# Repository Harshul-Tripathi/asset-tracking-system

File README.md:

# Anti-Theft Tracking

An industrial project developed in collaboration with **STMicroelectronics** to design and implement a highly accurate, multi-anchor asset tracking and anti-theft system utilizing Ultra-Wideband (UWB) technology that offers centimeter-level precision. 

This repository contains the complete firmware, hardware PCB designs, and comprehensive documentation for the entire project lifecycle.

---
## 👥 Contributors

*   Krishang Singh - Hardware selection, Schematic and Layout design, Low-power optimization
*   Krishna Kumar Mahto - Firmware, Qorvo SDK, Breadboard testing (one way ranging)
*   Harshul Tripathi - MCU Pinout Architecture (CubeMX), AirTag Analysis, System Power Profiling

## 🏗️ System Architecture

The tracking ecosystem relies on a 4-subsystem architecture designed for precise trilateration and efficient power management. The system consists of three stationary anchors and one mobile tag:

### 1. STM32 Anchor (Hub)
*   **Hardware:** NUCLEO-U575ZI-Q + BU03 (UWB Module) + ST67W611M (Wi-Fi Module)
*   **Role:** Acts as the central hub of the tracking system. It interfaces with the tag and the secondary ESP32 anchors to compute the final location of the asset and manage the network. It publishes this data to a dashboard through the ST67W611M Wi-Fi module.
*   **Location:** `firmware/stm32-anchor-hub/nucleo-u575zi-q_bu03/`

### 2. ESP32 Anchors (x2)
*   **Hardware:** ESP32 + UWB Modules
*   **Role:** Two secondary stationary anchors strategically placed to provide the additional reference points required for accurate 2D/3D trilateration. 
*   **Location:** `firmware/esp32-anchors/`

### 3. STM32 Tag
*   **Hardware:** NUCLEO-WBA55CG + BU03 (UWB Module) / Custom Compact PCB
*   **Role:** The mobile asset being tracked. Designed for a compact footprint, it broadcasts its signals to the anchor network.
*   **Location:** `firmware/stm32-tag/Nucleo-WBA55CG_BU03/`

---

## 📂 Repository Structure

The repository is modularized to separate different microcontrollers, hardware designs, and documentation, preventing workspace conflicts.

*   **`/docs`**: Contains all reference materials, component datasheets, project presentations, and research (including AirTag teardowns).
*   **`/firmware`**: Separated source code for the ESP-IDF and STM32CubeIDE workspaces. Each subsystem contains its own build instructions and configurations.
*   **`/hardware`**: Contains the custom compact tag PCB designs (KiCad/Altium). Includes standard EDA source files alongside a `/production` folder for manufacturing Gerbers and BOMs.
  ---

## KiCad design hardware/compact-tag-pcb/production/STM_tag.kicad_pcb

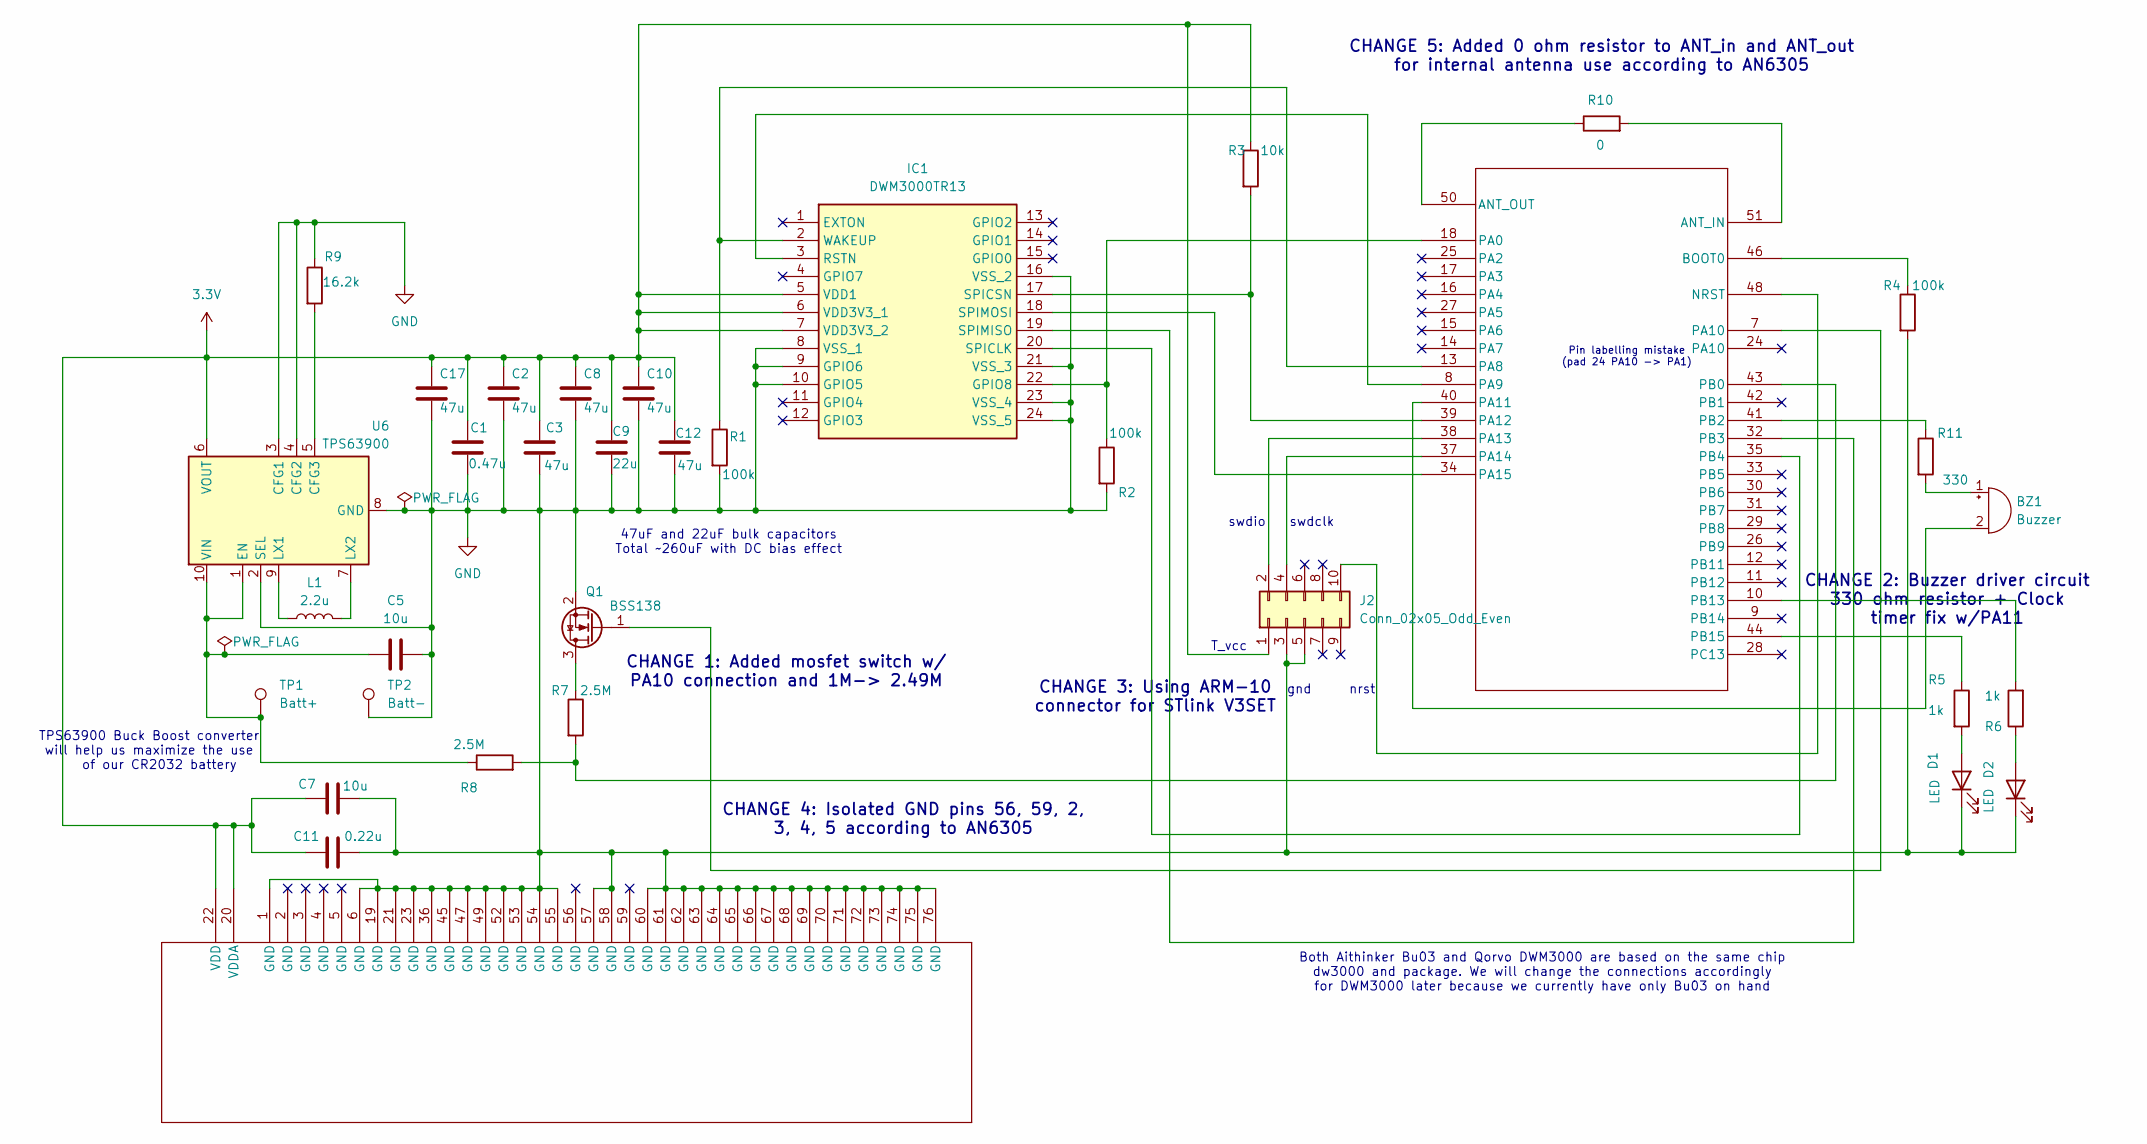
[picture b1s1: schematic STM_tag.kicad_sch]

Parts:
BZ1: Buzzer; AST0760_MAL
C1: 0.47u; C_0402_1005Metric
C2, C3, C8, C10, C12, C17: 47u; C_1206_3216Metric
C5, C7: 10u; C_0603_1608Metric
C9: 22u; C_0805_2012Metric
C11: 0.22u; C_0402_1005Metric
D1, D2: LED; LED_0402_1005Metric
IC1: DWM3000TR13; Manufacturer_Part_Number DWM3000TR13; Mouser Part Number 772-DWM3000TR13
J2: Conn_02x05_Odd_Even; PinHeader_2x05_P1.27mm_Vertical_SMD
L1: 2.2u; L_0603_1608Metric
Q1: BSS138; SOT-23
R1, R2, R4: 100k; R_0402_1005Metric
R3: 10k; R_0402_1005Metric
R5, R6: 1k; R_0402_1005Metric
R7, R8: 2.5M; R_0402_1005Metric
R9: 16.2k; R_0402_1005Metric
R10: 0; R_0402_1005Metric
R11: 330; R_0402_1005Metric
TP1: Batt+; TestPoint_THTPad_1.0x1.0mm_Drill0.5mm
TP2: Batt-; TestPoint_THTPad_1.0x1.0mm_Drill0.5mm
U3: STM32WBA5MMGH6TR; SIP-LGA76_STM
U6: TPS63900; WSON-10-1EP_2.5x2.5mm_P0.5mm_EP1.2x2mm_ThermalVias

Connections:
3.3V: C1.1, C2.1, C3.1, C7.1, C8.1, C9.1, C10.1, C11.1, C12.1, C17.1, IC1.5 (VDD1), IC1.6 (VDD3V3_1), IC1.7 (VDD3V3_2), J2.1, R3.1, U3.20 (VDDA), U3.22 (VDD), U6.6 (VOUT)
GND: C1.2, C2.2, C3.2, C5.2, C7.2, C8.2, C9.2, C10.2, C11.2, C12.2, C17.2, D1.1 (K), D2.1 (K), IC1.8 (VSS_1), IC1.9 (GPIO6), IC1.10 (GPIO5), IC1.16 (VSS_2), IC1.21 (VSS_3), IC1.23 (VSS_4), IC1.24 (VSS_5), J2.3, J2.5, Q1.2 (S), R1.2, R2.2, R4.2, R9.1, TP2.1, U3.1 (GND), U3.6 (GND), U3.19 (GND), U3.21 (GND), U3.23 (GND), U3.36 (GND), U3.45 (GND), U3.47 (GND), U3.49 (GND), U3.52 (GND), U3.53 (GND), U3.54 (GND), U3.55 (GND), U3.57 (GND), U3.58 (GND), U3.60 (GND), U3.61 (GND), U3.62 (GND), U3.63 (GND), U3.64 (GND), U3.65 (GND), U3.66 (GND), U3.67 (GND), U3.68 (GND), U3.69 (GND), U3.70 (GND), U3.71 (GND), U3.72 (GND), U3.73 (GND), U3.74 (GND), U3.75 (GND), U3.76 (GND), U6.2 (SEL), U6.3 (CFG1), U6.4 (CFG2), U6.8 (GND), U6.11 (GND)
unnamed: BZ1.1 (+), R11.2
unnamed: BZ1.2 (-), U3.40 (PA11)
unnamed: D1.2 (A), R5.2
unnamed: D2.2 (A), R6.1
unnamed: IC1.22 (GPIO8), R2.1, U3.18 (PA0)
unnamed: IC1.3 (RSTN), U3.8 (PA9)
unnamed: IC1.20 (SPICLK), U3.35 (PB4)
unnamed: IC1.17 (SPICSN), R3.2, U3.39 (PA12)
unnamed: IC1.19 (SPIMISO), U3.32 (PB3)
unnamed: IC1.18 (SPIMOSI), U3.34 (PA15)
unnamed: IC1.2 (WAKEUP), R1.1, U3.13 (PA8)
unnamed: J2.2, U3.38 (PA13)
unnamed: J2.4, U3.37 (PA14)
unnamed: J2.10, U3.48 (NRST)
unnamed: Q1.3 (D), R7.1
unnamed: Q1.1 (G), U3.7 (PA10)
unnamed: R10.2, U3.51 (ANT_IN)
unnamed: R10.1, U3.50 (ANT_OUT)
unnamed: R4.1, U3.46 (BOOT0)
unnamed: R7.2, R8.2, U3.43 (PB0)
unnamed: R11.1, U3.41 (PB2)
unnamed: R6.2, U3.10 (PB13)
unnamed: R5.1, U3.44 (PB15)
unnamed: R9.2, U6.5 (CFG3)
unnamed: C5.1, R8.1, TP1.1, U6.1 (EN), U6.10 (VIN)
unnamed: L1.1, U6.9 (LX1)
unnamed: L1.2, U6.7 (LX2)

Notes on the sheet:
swdclk
CHANGE 4: Isolated GND pins 56, 59, 2, 3, 4, 5 according to AN6305
47uF and 22uF bulk capacitors Total ~260uF with DC bias effect
CHANGE 2: Buzzer driver circuit 330 ohm resistor + Clock timer fix w/PA11
Pin labelling mistake (pad 24 PA10 -> PA1)
CHANGE 3: Using ARM-10 connector for STlink V3SET
CHANGE 1: Added mosfet switch w/ PA10 connection and 1M-> 2.49M
gnd
TPS63900 Buck Boost converter will help us maximize the use of our CR2032 battery
nrst
CHANGE 5: Added 0 ohm resistor to ANT_in and ANT_out for internal antenna use according to AN6305
swdio
T_vcc
Both Aithinker Bu03 and Qorvo DWM3000 are based on the same chip dw3000 and package. We will change the connections accordingly for DWM3000 later because we currently have only Bu03 on hand

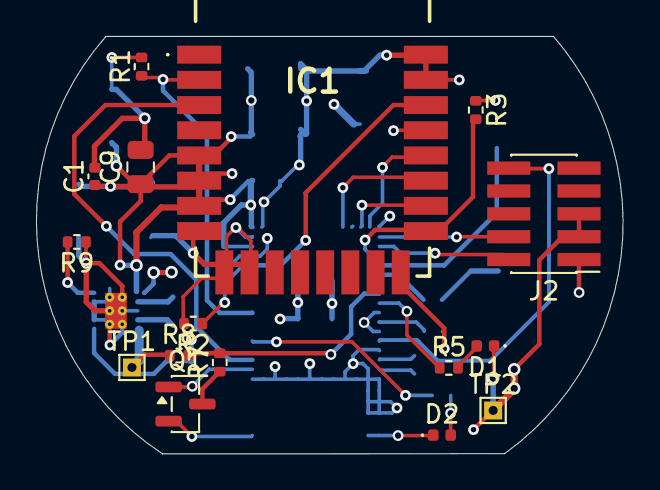
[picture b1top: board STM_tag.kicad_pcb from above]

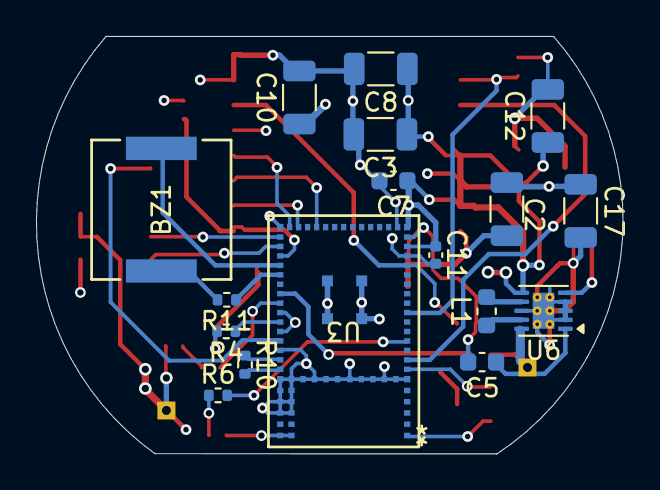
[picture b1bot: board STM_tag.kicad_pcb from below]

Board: 4 copper layers, 32.6 x 23.2 mm, 33 parts (17 on the bottom side), 29 nets.
